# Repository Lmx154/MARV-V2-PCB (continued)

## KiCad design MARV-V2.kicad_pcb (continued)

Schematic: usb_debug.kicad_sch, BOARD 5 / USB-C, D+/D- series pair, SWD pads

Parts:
C7: 1u / 10 V X7R 0402; C_0402_1005Metric; LCSC C52923
C49: 100n / 16 V X7R, ADC0; C_0402_1005Metric; LCSC C1525
D21: LED white 0603, USB power; LED_0603_1608Metric; LCSC C2290
J4: USB_C_PROGRAM_POWER; USB_C_Receptacle_HRO_TYPE-C-31-M-12; LCSC C165948
J10: SWD header 1x03 2.54 mm (SWCLK GND SWDIO); PinHeader_1x03_P2.54mm_Vertical
R4, R5: 5.1k / 1%; R_0402_1005Metric; LCSC C25905
R22: 22 / 1%, USB D+ series; R_0402_1005Metric; LCSC C25092
R23: 22 / 1%, USB D- series; R_0402_1005Metric; LCSC C25092
R29: 10k / 1%, VBUS top; R_0402_1005Metric; LCSC C25744
R30: 15k / 1%, VBUS bottom; R_0402_1005Metric; LCSC C25756
R56: 1k / 1%, USB LED series; R_0402_1005Metric; LCSC C11702

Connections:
GND: C7.2, C49.2, D21.1 (K), J4.A1 (GND), J4.A12 (GND), J4.B1 (GND), J4.B12 (GND), J4.SH (SHIELD), J10.2, R4.2, R5.2, R30.2; also elsewhere on the board
SWCLK: J10.1; also elsewhere on the board
SWDIO: J10.3; also elsewhere on the board
USB_CC1: J4.A5 (CC1), R4.1
USB_CC2: J4.B5 (CC2), R5.1
USB_D+: J4.A6 (D+), J4.B6 (D+), R22.1
USB_D-: J4.A7 (D-), J4.B7 (D-), R23.1
USB_LED_A: D21.2 (A), R56.2
USB_RP_D+: R22.2; also elsewhere on the board
USB_RP_D-: R23.2; also elsewhere on the board
USB_VBUS: C7.1, J4.A4 (VBUS), J4.A9 (VBUS), J4.B4 (VBUS), J4.B9 (VBUS), R29.1, R56.1; also elsewhere on the board
VBUS_SENSE: C49.1, R29.2, R30.1; also elsewhere on the board

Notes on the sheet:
VBUS_SENSE divider (10k / 15k)
D+/D- series pair - no ESD array
D21 / R56 - USB POWER INDICATOR, THE ONLY LED ON THIS BOARD BESIDES THE WS2812C. USB_VBUS -> R56 1 k -> USB_LED_A -> D21 anode, cathode to GND, so it lights whenever a host is plugged in and is dark on BEC-only power - which is exactly the question a bench user asks of this connector, and one the R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
USB_VBUS feeds the D1 Schottky and the Q1 gate on POWER 2 directly; no inrush or current limiting on this sheet, and no data ESD array - a USBLC6-2SC6 is JLC Extended and is not fitted, so D+/D- go straight from J4 into the 27 R series pair R22/R23, as on the madflight FC3v2. The RP2354B USB pins c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
SWD header
CC pull-downs
BOARD 5 - J4 USB-C 2.0 RECEPTACLE, THE 27 R D+/D- SERIES PAIR, THE VBUS SENSE DIVIDER AND THE J10 SWD HEADER. NO ON-BOARD USB ESD ARRAY.
USB-C receptacle
J10 is a 3-pin 2.54 mm SWD header (SWCLK / GND / SWDIO, Raspberry Pi Debug Probe order), not a 10-pin Cortex header; it is shipped unpopulated for the owner to solder (DESIGN_SPEC "Design decisions"). There is no debugger reference 3V3 pin and no debugger-driven reset line - power the board from th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
USB power LED

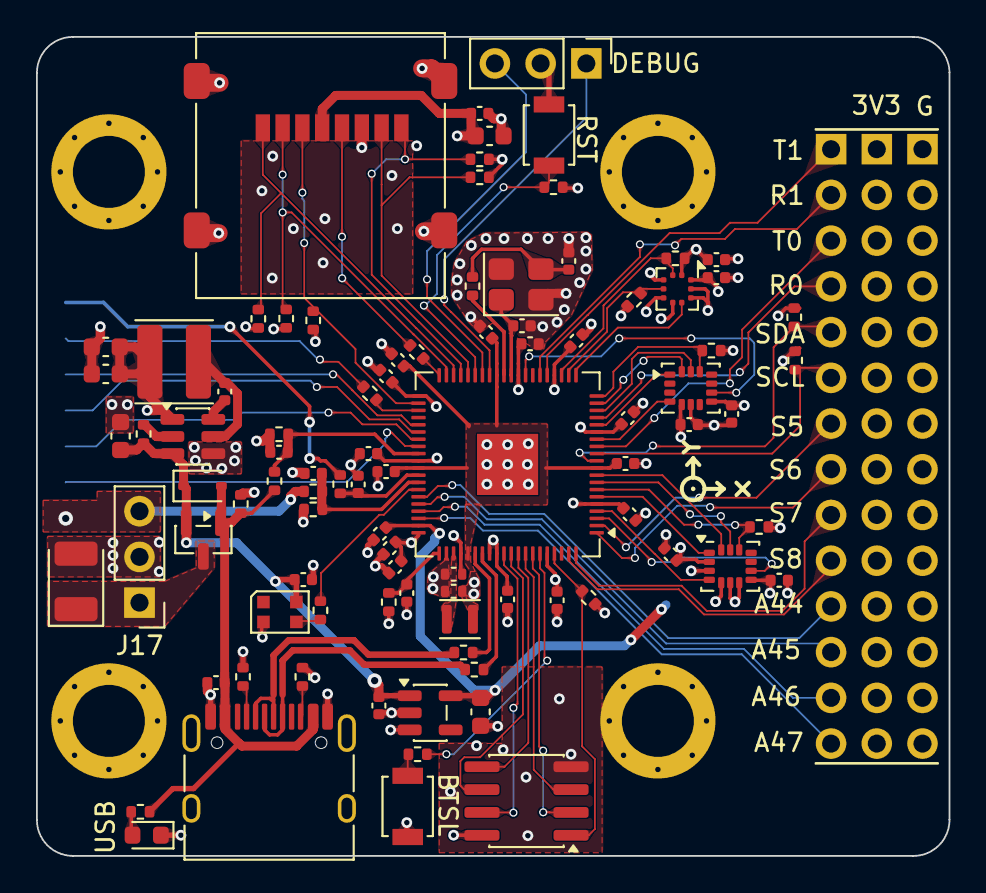
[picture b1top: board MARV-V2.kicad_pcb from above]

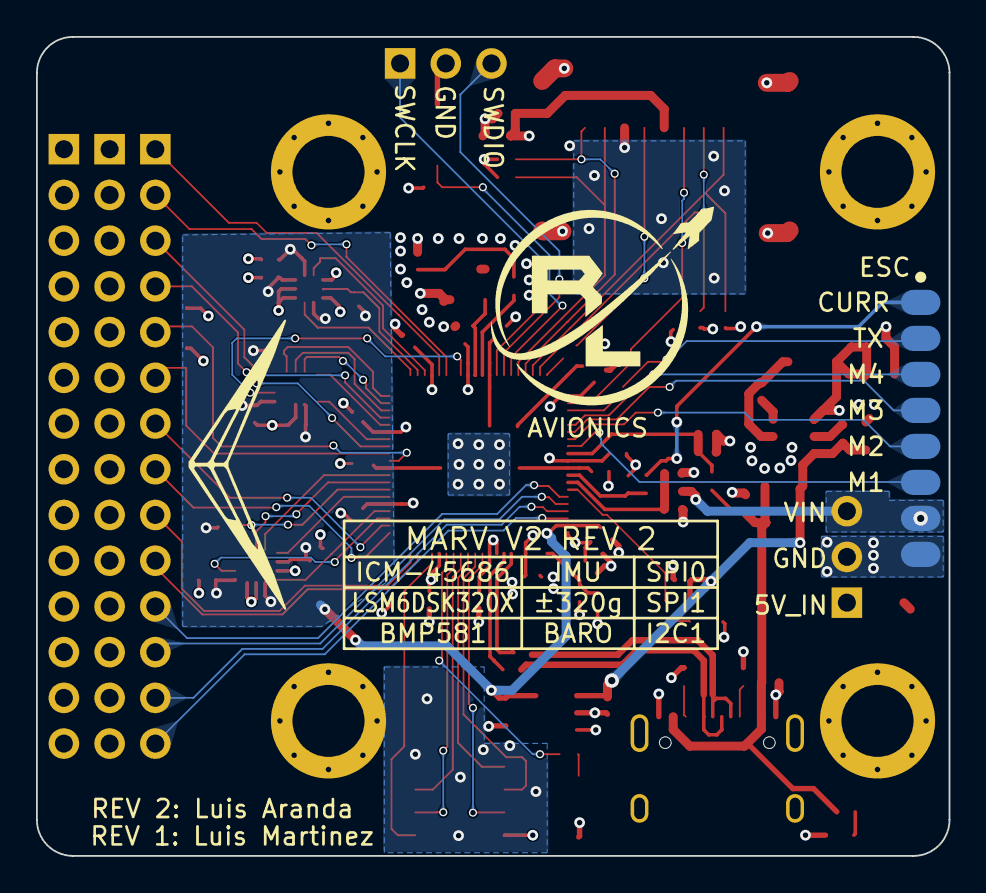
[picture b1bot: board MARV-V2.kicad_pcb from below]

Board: 4 copper layers, 50.7 x 45.5 mm, 103 parts (4 on the bottom side), 82 nets.

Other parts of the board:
G1: Logo_AxisMarker
G2: Logo_Chevron
G3: Info_SensorTable
G4: Logo_OrbitRocketRL

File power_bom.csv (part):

Reference,Value,Footprint,Sheet,Fit
"J3","ESC pads (CURR TX M4 M3 M2 M1 5V GND VBAT)","MARV_Packages:PadRow_1x09_P2.00mm","power_vbat","populated"
"C19","100u / 6.3 V polymer, ESR <= 40 mOhm (e.g. Panasonic 6TPE100MAZB or KEMET T520/T530 B case), 5V_IN bulk at the pad row","Capacitor_Tantalum_SMD:CP_EIA-3528-21_Kemet-B","power_vbat","populated"
"R53","1k / 1%, CURR series","Resistor_SMD:R_0402_1005Metric","power_vbat","populated"
"C78","100n / 16 V X7R, ADC2 filter","Capacitor_SMD:C_0402_1005Metric","power_vbat","populated"
"R54","1k, ESC telemetry series","Resistor_SMD:R_0402_1005Metric","power_vbat","populated"
"R27","100k / 1%, VBAT top","Resistor_SMD:R_0402_1005Metric","power_vbat","populated"
"R28","10k / 1%, VBAT bottom","Resistor_SMD:R_0402_1005Metric","power_vbat","populated"
"C48","100n / 16 V X7R, ADC1","Capacitor_SMD:C_0402_1005Metric","power_vbat","populated"
"Q1","AO3401A","Package_TO_SOT_SMD:SOT-23","power_or","populated"
"R7","100k / 1%, Q1 gate pull-down","Resistor_SMD:R_0402_1005Metric","power_or","populated"
"D1","1N5819WS","Diode_SMD:D_SOD-323","power_or","populated"
"C8","10u / 10 V X7R 0603, VIN bulk (AP63203 Table 2 C1)","Capacitor_SMD:C_0603_1608Metric","power_3v3","populated"
"U7","AP63203WU-7","Package_TO_SOT_SMD:TSOT-23-6","power_3v3","populated"
"R52","100k / 1%, EN to VIN","Resistor_SMD:R_0402_1005Metric","power_3v3","populated"
"C13","100n / 16 V X7R, bootstrap BST-SW (AP63203 Table 2 C3)","Capacitor_SMD:C_0402_1005Metric","power_3v3","populated"
"L2","4.7u, Isat 6.0 A (30 %), DCR 46 mOhm max (CJIANG FTC404030S4R7MGCA)","MARV_Packages:L_Changjiang_FTC404030S","power_3v3","populated"
"C10","22u / 10 V X5R 0603 GRM188R61A226ME15, COUT (~40% DC-bias loss at 3.3 V)","Capacitor_SMD:C_0603_1608Metric","power_3v3","populated"
"C11","22u / 10 V X5R 0603 GRM188R61A226ME15, COUT (~40% DC-bias loss at 3.3 V)","Capacitor_SMD:C_0603_1608Metric","power_3v3","populated"
"U12","TPS7A2033PDBVR","Package_TO_SOT_SMD:SOT-23-5","power_3v3","populated"
"C25","1u / 10 V X7R 0402, LDO input","Capacitor_SMD:C_0402_1005Metric","power_3v3","populated"
"C26","2.2u / 16 V X5R 0603, LDO output (>=1 uF effective, SBVS338H Sec 7.1.1)","Capacitor_SMD:C_0603_1608Metric","power_3v3","populated"
"U20","RP2354B","MARV_Packages:QFN-80-1EP_10x10mm_P0.4mm_EP3.4x3.4mm","mcu","populated"
"C39","4.7u / 10 V X5R 0402, VREG_VIN","Capacitor_SMD:C_0402_1005Metric","mcu","populated"
"C30","100n / 16 V X7R, IOVDD pin 5","Capacitor_SMD:C_0402_1005Metric","mcu","populated"
"C31","100n / 16 V X7R, IOVDD pin 15","Capacitor_SMD:C_0402_1005Metric","mcu","populated"
"C32","100n / 16 V X7R, IOVDD pin 24","Capacitor_SMD:C_0402_1005Metric","mcu","populated"
"C33","100n / 16 V X7R, IOVDD pin 29","Capacitor_SMD:C_0402_1005Metric","mcu","populated"
"C34","100n / 16 V X7R, IOVDD pin 41","Capacitor_SMD:C_0402_1005Metric","mcu","populated"
"C35","100n / 16 V X7R, IOVDD pin 50","Capacitor_SMD:C_0402_1005Metric","mcu","populated"
"C36","100n / 16 V X7R, IOVDD pin 60","Capacitor_SMD:C_0402_1005Metric","mcu","populated"
"C37","100n / 16 V X7R, IOVDD pin 76","Capacitor_SMD:C_0402_1005Metric","mcu","populated"
"C38","100n / 16 V X7R, pins 68+69","Capacitor_SMD:C_0402_1005Metric","mcu","populated"
"C40","100n / 16 V X7R, ADC_AVDD","Capacitor_SMD:C_0402_1005Metric","mcu","populated"
"R20","33 / 1%, VREG_AVDD filter","Resistor_SMD:R_0402_1005Metric","mcu","populated"
"C41","4.7u / 10 V X5R 0402, VREG_AVDD","Capacitor_SMD:C_0402_1005Metric","mcu","populated"
"L20","3.3u, 0806 AOTA-B201610S3R3-101-T","Inductor_SMD:L_Murata_DFE201610P","mcu","populated"
"C42","100n / 16 V X7R, DVDD pin 10","Capacitor_SMD:C_0402_1005Metric","mcu","populated"
"C43","100n / 16 V X7R, DVDD pin 32","Capacitor_SMD:C_0402_1005Metric","mcu","populated"
"C44","100n / 16 V X7R, DVDD pin 51","Capacitor_SMD:C_0402_1005Metric","mcu","populated"
"C45","4.7u / 10 V X5R 0402, DVDD bulk","Capacitor_SMD:C_0402_1005Metric","mcu","populated"
"C81","4.7u / 10 V X5R 0402, DVDD second bulk, far edge of U20 (RP2350 ds 6.3.8.1)","Capacitor_SMD:C_0402_1005Metric","mcu","populated"
"SW1","RESET (RUN to GND)","Button_Switch_SMD:SW_SPST_B3U-1000P","mcu","populated"
"R10","100k, RUN pull-up","Resistor_SMD:R_0402_1005Metric","mcu","populated"
"R24","1k, BOOTSEL strap","Resistor_SMD:R_0402_1005Metric","mcu","populated"
"SW2","BOOTSEL (via R24)","Button_Switch_SMD:SW_SPST_B3U-1000P","mcu","populated"
"Y1","12 MHz TAXM12M4RFBCCT2T, CL 12 pF","Crystal:Crystal_SMD_3225-4Pin_3.2x2.5mm","mcu","populated"
"C46","18p / 50 V C0G","Capacitor_SMD:C_0402_1005Metric","mcu","populated"
"R21","1k / 1%, crystal drive limit","Resistor_SMD:R_0402_1005Metric","mcu","populated"
"C47","18p / 50 V C0G","Capacitor_SMD:C_0402_1005Metric","mcu","populated"
"R25","4.7k, I2C1 SDA pull-up","Resistor_SMD:R_0402_1005Metric","mcu","populated"
"R26","4.7k, I2C1 SCL pull-up","Resistor_SMD:R_0402_1005Metric","mcu","populated"
"J4","USB_C_PROGRAM_POWER","MARV_Packages:USB_C_Receptacle_HRO_TYPE-C-31-M-12","usb_debug","populated"
"C7","1u / 10 V X7R 0402","Capacitor_SMD:C_0402_1005Metric","usb_debug","populated"
"R4","5.1k / 1%","Resistor_SMD:R_0402_1005Metric","usb_debug","populated"
"R5","5.1k / 1%","Resistor_SMD:R_0402_1005Metric","usb_debug","populated"
"R23","27 / 1%, USB D- series","Resistor_SMD:R_0402_1005Metric","usb_debug","populated"
"R22","27 / 1%, USB D+ series","Resistor_SMD:R_0402_1005Metric","usb_debug","populated"
"R29","10k / 1%, VBUS top","Resistor_SMD:R_0402_1005Metric","usb_debug","populated"
"R30","15k / 1%, VBUS bottom","Resistor_SMD:R_0402_1005Metric","usb_debug","populated"
"C49","100n / 16 V X7R, ADC0","Capacitor_SMD:C_0402_1005Metric","usb_debug","populated"
"R56","1k / 1%, USB LED series","Resistor_SMD:R_0402_1005Metric","usb_debug","populated"
"D21","LED white 0603, USB power","LED_SMD:LED_0603_1608Metric","usb_debug","populated"
"J10","SWD header 1x03 2.54 mm (SWCLK GND SWDIO)","Connector_PinHeader_2.54mm:PinHeader_1x03_P2.54mm_Vertical","usb_debug","populated"
"U21","ICM-45686 6-axis IMU","MARV_Packages:InvenSense_LGA-14_2.5x3mm_P0.5mm_ICM45686","imu","populated"
"C50","100n / 16 V X7R, U21 VDD","Capacitor_SMD:C_0402_1005Metric","imu","populated"
"C52","100n / 16 V X7R, U21 VDDIO","Capacitor_SMD:C_0402_1005Metric","imu","populated"
"R48","10k, ICM_CS pull-up","Resistor_SMD:R_0402_1005Metric","imu","populated"
"TP1","TP ICM_SCK","TestPoint:TestPoint_Pad_1.0x1.0mm","imu","populated"
"TP2","TP ICM_MOSI","TestPoint:TestPoint_Pad_1.0x1.0mm","imu","populated"
"TP3","TP ICM_MISO","TestPoint:TestPoint_Pad_1.0x1.0mm","imu","populated"
"TP4","TP ICM_CS","TestPoint:TestPoint_Pad_1.0x1.0mm","imu","populated"
"TP7","TP ICM_INT1","TestPoint:TestPoint_Pad_1.0x1.0mm","imu","populated"
"TP8","TP ICM_INT2","TestPoint:TestPoint_Pad_1.0x1.0mm","imu","populated"
"U22","BMP581 barometer","MARV_Packages:Bosch_LGA-10_2x2mm_BMP581","baro","populated"
"C54","100n / 16 V X7R, U22 VDD","Capacitor_SMD:C_0402_1005Metric","baro","populated"
"C56","100n / 16 V X7R, U22 VDDIO","Capacitor_SMD:C_0402_1005Metric","baro","populated"
"R50","4.7k","Resistor_SMD:R_0402_1005Metric","baro","populated"
"TP5","TP BARO_SDA","TestPoint:TestPoint_Pad_1.0x1.0mm","baro","populated"
"TP9","TP BARO_INT","TestPoint:TestPoint_Pad_1.0x1.0mm","baro","populated"
"U23","ADXL375 high-g accelerometer","MARV_Packages:Analog_LGA-14_3x5mm_P0.8mm_ADXL375","highg","populated"
"C59","1u / 10 V X7R 0402, U23 VS","Capacitor_SMD:C_0402_1005Metric","highg","populated"
"C60","100n / 16 V X7R, U23 VDD_IO","Capacitor_SMD:C_0402_1005Metric","highg","populated"
"R51","10k, ADXL_CS pull-up","Resistor_SMD:R_0402_1005Metric","highg","populated"
"TP6","TP ADXL_CS","TestPoint:TestPoint_Pad_1.0x1.0mm","highg","populated"
"TP10","TP ADXL_INT1","TestPoint:TestPoint_Pad_1.0x1.0mm","highg","populated"
"J11","microSD, Molex 47219-2001 locking hinge","MARV_Packages:microSD_HC_Molex_47219-2001","sd","populated"
"R39","10k, SD_DAT2 pull-up","Resistor_SMD:R_0402_1005Metric","sd","populated"
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
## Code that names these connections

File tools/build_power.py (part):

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
# (package pin, GPIO name, net or None for no-connect, function note)
MCU_GPIO=[
 ('77','GPIO0','FLASH_CS1','QMI CS1n, log flash select'),
 ('78','GPIO1','HG_ACC_INT','ADXL375 INT1'),
 ('79','GPIO2','IMU_INT2','ICM-45686 INT2/FSYNC/CLKIN'),
 ('80','GPIO3','LED_DATA','WS2812C-2020 data, 100 R series (R55)'),
 ('1','GPIO4','HG_ACC_CS','ADXL375 CS'),
 ('2','GPIO5','PWM8','PWM2 B -> J6 row 10 (S8)'),
 ('3','GPIO6','IMU_INT1','ICM-45686 INT1'),
 ('4','GPIO7','IMU_CS','ICM-45686 AP_CS'),
 ('6','GPIO8','SENS_MISO','SPI1 RX'),
 ('7','GPIO9',None,'unexposed spare - no connect'),
 ('8','GPIO10','SENS_SCK','SPI1 SCK'),
 ('9','GPIO11','SENS_MOSI','SPI1 TX'),
 ('11','GPIO12',None,'unexposed spare - no connect'),
 ('12','GPIO13','BARO_INT','BMP581 INT'),
 ('13','GPIO14','BARO_CS','BMP581 CSB'),
 ('14','GPIO15','PWM7','PWM7 B -> J6 row 9 (S7)'),
 ('16','GPIO16','ELRS_RX','UART0 TX -> radio RX'),
 ('17','GPIO17','ELRS_TX','UART0 RX <- radio TX'),
 ('18','GPIO18',None,'unexposed spare - no connect'),
 ('19','GPIO19','PWM6','PWM1 B -> J6 row 8 (S6)'),
 ('20','GPIO20','PWM5','PWM2 A -> J6 row 7 (S5)'),
 ('21','GPIO21',None,'unexposed spare - no connect'),
 ('22','GPIO22','MAG_SDA','I2C1 SDA'),
 ('23','GPIO23','MAG_SCL','I2C1 SCL'),
 ('25','GPIO24','GPS_RX','UART1 TX -> GPS RX'),
 ('26','GPIO25','GPS_TX','UART1 RX <- GPS TX'),
 ('27','GPIO26',None,'unexposed spare - no connect'),
 ('28','GPIO27',None,'unexposed spare - no connect'),
 ('36','GPIO28','SD_D0','microSD DAT0 (PIO, GPIOBASE 16 window)'),
 ('37','GPIO29','SD_D1','microSD DAT1 (PIO, GPIOBASE 16 window)'),
 ('38','GPIO30','SD_D2','microSD DAT2 (PIO, GPIOBASE 16 window)'),
 ('39','GPIO31','SD_D3','microSD DAT3 (PIO, GPIOBASE 16 window)'),
 ('40','GPIO32','ESC_TELEM_RX','ESC KISS telemetry in (PIO UART RX, window 16-47), 1k series R54'),
 ('42','GPIO33','SD_CLK','microSD CLK (PIO, GPIOBASE 16 window)'),
 ('43','GPIO34','SD_CMD','microSD CMD (PIO, GPIOBASE 16 window)'),
 ('44','GPIO35','SD_DET','microSD card detect'),
 ('45','GPIO36','PWM4','DShot via PIO (window 16-47)'),
 ('46','GPIO37',None,'unexposed spare - no connect (was PWR_SRC_ST; the mux is gone)'),
 ('47','GPIO38','PWM3','DShot via PIO (window 16-47)'),
 ('48','GPIO39','PWM2','DShot via PIO (window 16-47)'),
 ('49','GPIO40','VBUS_SENSE','ADC0, USB_VBUS 10k/15k divider'),
 ('52','GPIO41','VBAT_SENSE','ADC1, VBAT 100k/10k divider, 36.3 V FS'),
 ('53','GPIO42','CURR_SENSE','ADC2, ESC current sense, 1k + 100n'),
 ('54','GPIO43','PWM1','DShot via PIO (window 16-47)'),
 ('55','GPIO44','IO_GPIO44','ADC4 -> J6 row 11 (A44)'),
 ('56','GPIO45','IO_GPIO45','ADC5 -> J6 row 12 (A45)'),
 ('57','GPIO46','IO_GPIO46','ADC6 -> J6 row 13 (A46)'),
 ('58','GPIO47','IO_GPIO47','ADC7 -> J6 row 14 (A47)'),
]

# ---------------------------------------------------------------------------
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# parked in the margin of the page they belong to (see Sheet.note).
# ---------------------------------------------------------------------------
N_MCU_HDR = ('RP2354B, QFN-80, 2 MB in-package QSPI flash. Digital rails on V3V3_SYS, core DVDD from the on-chip buck.\n'
    'RAIL SPLIT: V3V3_ANA (TPS7A20 LDO) now feeds exactly one RP2354B pin - ADC_AVDD (pin 59, with C40). The core regulator input\n'
    'filter R20/C41 that produces VREG_AVDD is fed from V3V3_SYS instead, so the buck-converter reference current no longer flows out\n'
    'of the low-noise analog rail and the sensors do not share a rail with it; V3V3_ANA is left carrying only ADC_AVDD and the MEMS.\n'
    'Decoupling, core regulator, crystal and BOOTSEL follow the RP2350 hardware design guide; every pin net is a global label.')
N_XTAL = ('Crystal circuit per design guide Sec 4. Y1 IS TAXM12M4RFBCCT2T (LCSC C133337), 12 MHz, SMD 3225 4-pad, CL = 12 pF - the\n'
    'ABM8-272-T3 the earlier revision named is not orderable at JLCPCB in any form (reports/jlc-audit.md section 1).\n'
    'LOAD CAPS FOLLOW THE CRYSTAL, NOT THE OTHER WAY ROUND: CL = C46*C47/(C46+C47) + Cstray, so C46/C47 are 18 pF C0G each\n'
    '(2 x 18 pF in series = 9 pF, plus ~3 pF of XIN/XTAL_DRV pin and trace stray = 12 pF, matching CL exactly). They were\n'
    '15 pF against the old CL 10 pF part; leaving 15 pF on a CL 12 pF crystal gives 10.5 pF of load, i.e. an under-loaded\n'
    'oscillator running fast by roughly the trim sensitivity of the part. The ~3 pF stray is the design-guide estimate and is\n'
    'the one term here that is not a datasheet number - if the board is ever pulled for frequency, that is the term to measure.\n'
    '1 k in the XOUT leg to limit drive with a 50 ohm ESR crystal. C38 is the single design-guide decoupling exception (pins 68+69 share it).\n'
    'VREG_AVDD RC = 33 ohm + 4.7 uF (design guide Sec 2.1), taken from V3V3_SYS; VREG_FB is tied to DVDD, VREG_PGND to GND, EP to GND.')
N_PORTNAMES = ('PORT NAMING: a port label is named for the peripheral pin it comes from, so GPS_TX / ELRS_TX are module outputs\n'
    'and land on MCU UART RX pins, while GPS_RX / ELRS_RX are module inputs fed by the MCU UART TX pins. On the IO\n'
    'array (POWER 3) the UART rows are therefore 1 GPS_RX (silk T0) / 2 GPS_TX (R0) / 3 ELRS_RX (T1) / 4 ELRS_TX (R1),\n'
    'rows 5/6 are MAG_SDA / MAG_SCL, rows 7-10 the PWM5-8 servo signals and rows 11-14 the four exposed spares.\n'
    'The array is three stacked 1x14 rows: J6 SIGNAL, J7 POWER, J8 GND. All array SIGNAL pins are 3.3 V CMOS.\n'
    'GPIO37 (pin 46) is SPARE and unconnected again: it used to read PWR_SRC_ST, the open-drain status output of\n'
    'the U25 TPS2121 mux, and the mux is gone. USB presence is already readable on the VBUS_SENSE divider (GPIO40).')
N_J10 = ('J10 is a 3-pad SWD landing (SWCLK / SWDIO / GND), not a 10-pin Cortex header: solder pads are kept for the two\n'
    'ports that mate with something fixed - the ESC row J3 and this one (DESIGN_SPEC "Connection philosophy").\n'
    'The debugger reference 3V3 and the debugger-driven reset line\n'
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    'THE PULL-UP IS NOW A PLAIN RESISTOR, not a regulator power-good output: the AP63203 has no PG pin, so the\n'
    'explicit "RUN cannot release before V3V3_SYS is in regulation" sequencing of the TPS62913 is gone. The\n'
    'RP2350 brown-out detector (always on, 8 threshold steps, design guide Sec 2.2) is what covers it instead.')
N_SPAREIO = ('SPARE IO. EXPOSED (IO array J6 signal column, POWER 3): GPIO44 row 11 (A44) | GPIO45 row 12 (A45) |\n'
    'GPIO46 row 13 (A46) | GPIO47 row 14 (A47). All four are ADC4-ADC7, which is why the silk labels are\n'
    'A44-A47 rather than IOnn; each sits next to a V3V3_SYS pin (J7) and a GND pin (J8) in the same row.\n'
    'UNEXPOSED, NO-CONNECT: GPIO9, GPIO12, GPIO18, GPIO21, GPIO26, GPIO27 carry a no-connect flag on this\n'
    'sheet - the 14-row array has no room for them once GPS/ELRS/I2C1/PWM5-8 and the four ADC spares are\n'
    'placed. They are left unconnected deliberately; exposing one means editing PINOUT.md, this generator\n'
    'and tools/check_power_netlist.py together. GPIO budget: 38 on board functions and ports, 4 spare on\n'
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    'VBAT_SENSE: R27/R28 100k/10k scale VBAT by 1/11, so the 3.3 V ADC full scale is 36.3 V. A 6S pack at its\n'
    '25.2 V maximum reads 2.29 V and a 2S pack at 6.0 V reads 0.55 V, so the whole 2-6S window is on-scale with\n'
    'headroom; the divider draws 229 uA at 25.2 V. The old 5V_IN divider is gone with the 5 V input itself.\n'
    'CURR_SENSE: the ESC current-sense output (J3 pin 1, 12.75 mV/A, 0-3.3 V) through R53 1k into C78 100 nF at\n'
    'the pin - a 100 us RC anti-alias/ESD network, well under the RP2350 ADC source-impedance guidance.\n'
    'ESC_TELEM: the ESC KISS telemetry output (J3 pin 2, 3.3 V, 115200 baud, one-wire from the ESC) through R54\n'
    '1k into GPIO32, read by a PIO UART (GPIOBASE 16 window). The resistor is series protection only, not a level\n'
    'shifter: the ESC pad row is 3.3 V CMOS on both the telemetry and the four motor lines.\n'
    'VBUS_SENSE keeps 10k/15k, now on GPIO40 (ADC0); VBAT_SENSE moved to GPIO41 (ADC1).\n'
    'D20 WS2812C-2020: VDD on V5_SYS with C79 100 nF, DIN from GPIO3 through R55 100 R, DOUT no-connect (single\n'
    'pixel). Its DIN VIH minimum is 2.7 V (datasheet Electrical Characteristics), which 3.3 V CMOS clears - that\n'
    'is why the C variant is used rather than a 5050 WS2812B, whose VIH is 0.7 x VDD = 3.5 V.\n'
    'QSPI_* are the dedicated QSPI pads: they reach the in-package flash die AND the package pins\n'
    '(RP2350 datasheet Sec 14.3), so U24 shares the bus with GPIO0/QMI CS1n (FLASH_CS1) as its select.\n'
    'RP2354 requires QSPI_IOVDD = 3.3 V, and IOVDD = 3.3 V to run a second QSPI device (Sec 14.9).')
N_SENS_HDR = ('All three sensors run 4-wire SPI on the shared SENS_SCK / SENS_MOSI / SENS_MISO bus with one chip select each,\n'
    'and are powered from V3V3_ANA (TPS7A20 LDO). Every supply pin on this sheet gets 100 nF + 1 uF: BMP581 and\n'
    'ADXL375 because their own datasheets call for the pair, the ICM-45686 as a deliberate addition - its\n'
    'datasheet BOM (DS-000577 Rev 1.0 Table 11) lists 0.1 uF only.')
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
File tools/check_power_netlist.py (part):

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    return None if n is None or n.startswith('unconnected-') else n

# Expected GPIO connections, maintained alongside the saved schematic and PINOUT.md.
# GPIO0-27 and GPIO35 follow the GPIO tables in PINOUT.md:
# GPIO1/26/35 are the three no-connect spares; they carry no-connect flags (None below).
# GPIO27 clocks the ICM-45686 CLKIN pin (net ICM_CLKIN, 32.000 kHz generated in firmware).
PINOUT={
 0:'FLASH_CS1', 1:None, 2:'PWM8', 3:'PWM7', 4:'PWM6', 5:'PWM5',
 6:'IMU2_INT2', 7:'IMU2_INT1', 8:'IMU2_MISO', 9:'IMU2_CS', 10:'IMU2_SCK', 11:'IMU2_MOSI',
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 24:'ELRS_RX', 25:'ELRS_TX', 26:None, 27:'ICM_CLKIN', 28:'SD_DAT0', 29:'SD_DAT1',
 30:'SD_DAT2', 31:'SD_DAT3', 32:'SD_CLK_MCU', 33:'SD_CMD', 34:'ESC_TELEM_RX', 35:None,
 36:'PWM4', 37:'PWM3', 38:'PWM2', 39:'PWM1', 40:'VBUS_SENSE', 41:'CURR_SENSE',
 42:'VBAT_SENSE', 43:'LED_DATA', 44:'IO_GPIO44', 45:'IO_GPIO45', 46:'IO_GPIO46', 47:'IO_GPIO47',
}

# RP2354B GPIO-to-package-pad mapping.
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 ('C8','1'):'V5_SYS',('C8','2'):'GND',
 ('C10','1'):'V3V3_SYS',('C10','2'):'GND',('C11','1'):'V3V3_SYS',('C11','2'):'GND',
 ('R52','1'):'V5_SYS',('R52','2'):'U7_EN',
 # U12 TPS7A20 LDO: EN (pin 3) is tied to V3V3_SYS itself.  The AP63203 has no power-good output,
 # so the rail does the buck-before-LDO sequencing instead of a status pin.
 ('U12','1'):'V5_SYS',('U12','2'):'GND',('U12','3'):'V3V3_SYS',('U12','5'):'V3V3_ANA',
 ('J4','A5'):'USB_CC1',('J4','B5'):'USB_CC2',('J4','SH'):'GND',
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 ('R10','1'):'V3V3_SYS',('R10','2'):'MCU_RUN',('SW1','1'):'MCU_RUN',('SW1','2'):'GND',
 # ESC analog current sense and one-wire KISS telemetry, both conditioned by a 1k series resistor
 ('R53','1'):'CURR_SENSE_RAW',('R53','2'):'CURR_SENSE',('C78','1'):'CURR_SENSE',('C78','2'):'GND',
 ('U20','52'):'CURR_SENSE',                                       # GPIO41 = ADC1
 ('R54','1'):'ESC_TELEM',('R54','2'):'ESC_TELEM_RX',('U20','43'):'ESC_TELEM_RX',   # GPIO34, PIO UART RX
 # WS2812C-2020 (LED:WS2812B-2020 symbol): 1 DOUT (no connect), 2 VSS, 3 DIN, 4 VDD
 ('R55','1'):'LED_DATA',('R55','2'):'LED_DIN',('U20','54'):'LED_DATA',
 ('D20','2'):'GND',('D20','3'):'LED_DIN',('D20','4'):'V5_SYS',('C79','1'):'V5_SYS',('C79','2'):'GND',
 # SWD header, Raspberry Pi Debug Probe order (SWCLK, GND, SWDIO)
 ('J10','1'):'SWCLK',('J10','2'):'GND',('J10','3'):'SWDIO',
 # the RP2354B end of the four spare GPIOs that leave on the IO block (rows 11-14)
 ('U20','55'):'IO_GPIO44',('U20','56'):'IO_GPIO45',('U20','57'):'IO_GPIO46',
 ('U20','58'):'IO_GPIO47',
 # RP2354B rails (MCU sheet). ADC_AVDD (59) stays on the LDO rail; the VREG_AVDD RC filter is fed
 # from V3V3_SYS, so R20 pin 1 must be V3V3_SYS and pin 61 must still reach it only through R20.
 ('U20','5'):'V3V3_SYS',('U20','59'):'V3V3_ANA',('U20','61'):'VREG_AVDD',
 ('U20','63'):'VREG_LX',('U20','64'):'V3V3_SYS',('U20','65'):'DVDD',
 ('U20','62'):'GND',('U20','81'):'GND',('U20','68'):'V3V3_SYS',('U20','69'):'V3V3_SYS',
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 ('C50','1'):'V3V3_ANA',('C50','2'):'GND',('C52','1'):'V3V3_ANA',('C52','2'):'GND',
 ('C54','1'):'V3V3_ANA',('C54','2'):'GND',('C56','1'):'V3V3_ANA',('C56','2'):'GND',
 ('C59','1'):'V3V3_ANA',('C59','2'):'GND',('C60','1'):'V3V3_ANA',('C60','2'):'GND',
 # U21 CLKIN (pin 9) is driven by U20 GPIO27 (pad 28), a firmware-generated 32.000 kHz clock (BUS_NODES);
 # the Rev 1 oscillator X1 and its cap C1 are gone (asserted absent below).
 ('U20','28'):'ICM_CLKIN',('U21','9'):'ICM_CLKIN',
 # THE USB POWER INDICATOR: USB_VBUS -> R56 1k -> USB_LED_A -> D21 anode (Device:LED
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 # logging supplies on the system rail
 ('U24','8'):'V3V3_SYS',('U24','4'):'GND',('J11','4'):'V3V3_SYS',('J11','6'):'GND',('J11','SH'):'GND',
 # port naming: the module TX lands on an MCU UART RX pin, the module RX on an MCU TX pin
 # (UART1 on GPIO24/25 carries ELRS; GPS is hardware UART0 on GPIO14 TX / GPIO17 RX)
 ('U20','17'):'GPS_TX',('U20','13'):'GPS_RX',('U20','26'):'ELRS_TX',('U20','25'):'ELRS_RX',
 ('U20','11'):'MAG_SDA',('U20','12'):'MAG_SCL',
}
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# one table that catches a mis-wired port, a signal on the wrong rail, or a 5 V pin on a 3.3 V row.
IO_ROWS=[('ELRS_RX','V3V3_SYS'),('ELRS_TX','V3V3_SYS'),('GPS_RX','V3V3_SYS'),('GPS_TX','V3V3_SYS'),
         ('MAG_SDA','V3V3_SYS'),('MAG_SCL','V3V3_SYS'),('PWM5','V3V3_SYS'),('PWM6','V3V3_SYS'),
         ('PWM7','V3V3_SYS'),('PWM8','V3V3_SYS'),('IO_GPIO44','V3V3_SYS'),('IO_GPIO45','V3V3_SYS'),
         ('IO_GPIO46','V3V3_SYS'),('IO_GPIO47','V3V3_SYS')]
for _i,(_sig,_pwr) in enumerate(IO_ROWS):
    expected[('J6',str(_i+1))]=_sig
    expected[('J7',str(_i+1))]=_pwr
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# power indicator on the usb_debug sheet (asserted above) and is not in this set.  BZ1 the
# through-hole buzzer, and with it the whole buzzer driver - J15 pads, Q20 gate, D22 flyback, R33/R34
# gate network - must be absent.
# X1 (the Rev 1 32.000 kHz CLKIN oscillator) and its 100 nF cap C1 are removed in Rev 2: GPIO27 drives
# ICM_CLKIN.
# J9 (MAG pad row), J16 (the 2x6 spare-IO block) and the J12/J13/J14 servo block are absent: PWM5-8
# are rows 7-10 of the IO block.  J7 and J8 are the power and GND columns of that block.
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# Rev 2 has NO do-not-populate part: U24 (the QSPI PSRAM, APS6404L-3SQN-SN) is fitted and in the BOM.  The
# land still accepts a W25Q32JVSNIQ NOR flash as an alternative fit.  C62, its bypass, is a 1 uF: the
# APS6404L REQUIRES a low-ESR 1 uF on VDD (its datasheet Sec 16.4) and the W25Q32JV names no supply
# capacitor at all, so one 1 uF serves both fits.  R35, the FLASH_CS1 pull-up, holds GPIO0 deselected.
_DNP = set()
_props = {c.get('ref'): {p.get('name') for p in c.findall('property')}
          for c in root.find('components')}
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# 3. V5_SYS is the OR output. It reaches no connector directly. Every IO block
#    row, GPS/ELRS included, is powered through the system buck. Its only loads are the two 3.3 V regulators and the WS2812 status LED (D20/C79,
#    <=60 mA, kept here deliberately so the LED works on USB-only bench power).
assert not {(ref,pin) for ref,pin in nets['V5_SYS'] if ref.startswith('J')},nets['V5_SYS']
assert nets['V5_SYS']=={('Q1','2'),('D1','1'),('U7','3'),('U12','1'),('R52','1'),
                        ('C8','1'),('C25','1'),('D20','4'),('C79','1')},nets['V5_SYS']
# 3z. The OR itself: the gate is USB_VBUS (so USB turns Q1 OFF), the diode anode is USB_VBUS, and
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assert not [n for n in nets if n in ('PWR_GOOD','PWR_SRC_ST','U7_VO','U7_FB','U7_SS','U7_SCONF',
                                     'U26_SW','U26_BST','U26_EN','U25_PR1','U25_OV1','U25_ILM',
                                     'U25_SS','USB_DP_MCU','USB_DM_MCU')],sorted(nets)
# 3a. V3V3_SYS supplies all fourteen IO power pins (J7 rows 1-14) and the
#     microSD socket; no other connector may carry the system rail.
assert {(ref,pin) for ref,pin in nets['V3V3_SYS'] if ref.startswith('J')}=={
    ('J7',str(p)) for p in range(1,15)} | {('J11','4')},nets['V3V3_SYS']
# 3b. The GND column is all ground, every pin of it, so every row has its own return.
assert {(ref,pin) for ref,pin in nets['GND'] if ref=='J8'}=={
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    assert {ref for ref,pin in nets['PWM%d'%n] if ref.startswith('J')}=={'J3'},nets['PWM%d'%n]
for n in range(5,9):
    assert {ref for ref,pin in nets['PWM%d'%n] if ref.startswith('J')}=={'J6'},nets['PWM%d'%n]
assert not any(ref.startswith('J') for ref,pin in nets['V3V3_ANA'])
# the RP2354B analog rail reaches VREG_AVDD only through the 33 ohm design-guide filter
assert nets['VREG_AVDD']=={('U20','61'),('R20','2'),('C41','1')},nets['VREG_AVDD']
assert ('U20','61') not in nets['V3V3_ANA']
# the log flash shares the dedicated QSPI pads and takes its select from GPIO0/QMI CS1n
for mcu,flash in [('71','6'),('72','5'),('74','2'),('73','3'),('70','7')]:
    assert pin_net[('U20',mcu)]==pin_net[('U24',flash)],(mcu,flash)
assert nets['FLASH_CS1']=={('U20','77'),('U24','1'),('R35','2')},nets['FLASH_CS1']
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 'ICM_MISO': {_U20(16),('U21','1')},
 'ICM_CS': {_U20(20),('U21','12'),('R48','2')},
 'ICM_INT1': {_U20(15),('U21','4')},
 # ICM pin 9 (INT2/FSYNC/CLKIN) is the 32.000 kHz clock input, driven by U20 GPIO27 (pad 28).
 'ICM_CLKIN': {('U21','9'),_U20(27)},
 'BARO_SCL': {_U20(23),('U22','2'),('R50','2')},
 'BARO_SDA': {_U20(22),('U22','4'),('R57','2')},
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}
for name, nodes in BUS_NODES.items():
    assert nets.get(name) == nodes, (name, nodes, nets.get(name))
assert pin_net[('U22','6')] == 'V3V3_ANA', 'BMP581 CSB must select I2C'
assert pin_net[('U22','5')] == 'GND', 'BMP581 address must be 0x46'
assert not any(n.startswith(('SENS_', 'HG_ACC_', 'IMU_')) or n == 'BARO_CS' for n in nets)
# RP2354B Table 3 / RP2350 Table 645: SPI0 RX16/SCK18/TX19 (ICM-45686), SPI1 RX8/CSn9/SCK10/TX11
# (LSM6DSK320X), I2C0 SDA12/SCL13 (MAG), I2C1 SDA22/SCL23 (BMP581), UART1 TX24/RX25 (ELRS),
# UART0 TX14 (F11 aux)/RX17 (F2) (GPS, hardware UART; no PIO UART for GPS). SD DAT pins increase
# consecutively; all six SD signals, the LED and the ESC PIO signals sit in the GPIO16-47 PIO window
# (GPIOBASE = 16).
assert [PINOUT[g] for g in (16,18,19)] == ['ICM_MISO','ICM_SCK','ICM_MOSI']
assert [PINOUT[g] for g in (8,10,11,9)] == ['IMU2_MISO','IMU2_SCK','IMU2_MOSI','IMU2_CS']
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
